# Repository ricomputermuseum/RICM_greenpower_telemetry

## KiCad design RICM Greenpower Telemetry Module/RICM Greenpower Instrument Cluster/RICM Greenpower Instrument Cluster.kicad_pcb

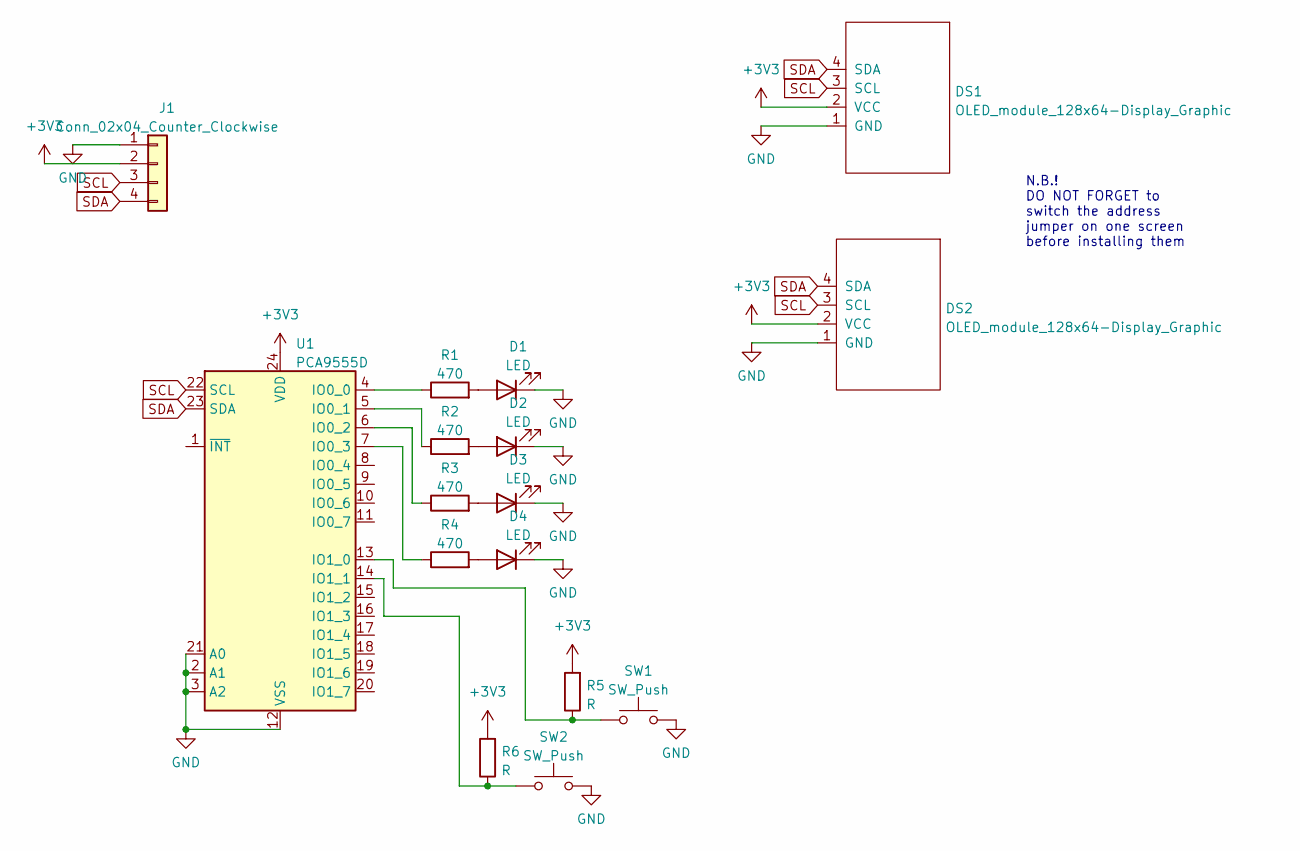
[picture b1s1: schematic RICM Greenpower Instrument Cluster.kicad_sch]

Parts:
D1, D2, D3, D4: LED; LED_D5.0mm
DS1, DS2: OLED_module_128x64-Display_Graphic; OLED__module_128x64
J1: Conn_02x04_Counter_Clockwise; PinHeader_1x04_P2.54mm_Vertical
R1, R2, R3, R4: 470; R_Axial_DIN0207_L6.3mm_D2.5mm_P7.62mm_Horizontal
R5, R6: R; R_Axial_DIN0207_L6.3mm_D2.5mm_P7.62mm_Horizontal
SW1, SW2: SW_Push; SW_PUSH_6mm_2pin
U1: PCA9555D; SOIC-24W_7.5x15.4mm_P1.27mm

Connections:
+3V3: DS1.2 (VCC), DS2.2 (VCC), J1.2, U1.24 (VDD)
+5V: R5.2, R6.2
GND: D1.1 (K), D2.1 (K), D3.1 (K), D4.1 (K), DS1.1 (GND), DS2.1 (GND), J1.1, SW1.2, SW2.2, U1.2 (A1), U1.3 (A2), U1.12 (VSS), U1.21 (A0)
unnamed: D1.2 (A), R1.2
unnamed: D2.2 (A), R2.2
unnamed: D3.2 (A), R3.2
unnamed: D4.2 (A), R4.2
unnamed: R1.1, U1.4 (IO0_0)
unnamed: R2.1, U1.5 (IO0_1)
unnamed: R3.1, U1.6 (IO0_2)
unnamed: R4.1, U1.7 (IO0_3)
unnamed: R5.1, SW1.1, U1.13 (IO1_0)
unnamed: R6.1, SW2.1, U1.14 (IO1_1)
SCL: DS1.3 (SCL), DS2.3 (SCL), J1.3, U1.22 (SCL)
SDA: DS1.4 (SDA), DS2.4 (SDA), J1.4, U1.23 (SDA)

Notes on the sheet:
N.B.! DO NOT FORGET to switch the address jumper on one screen before installing them

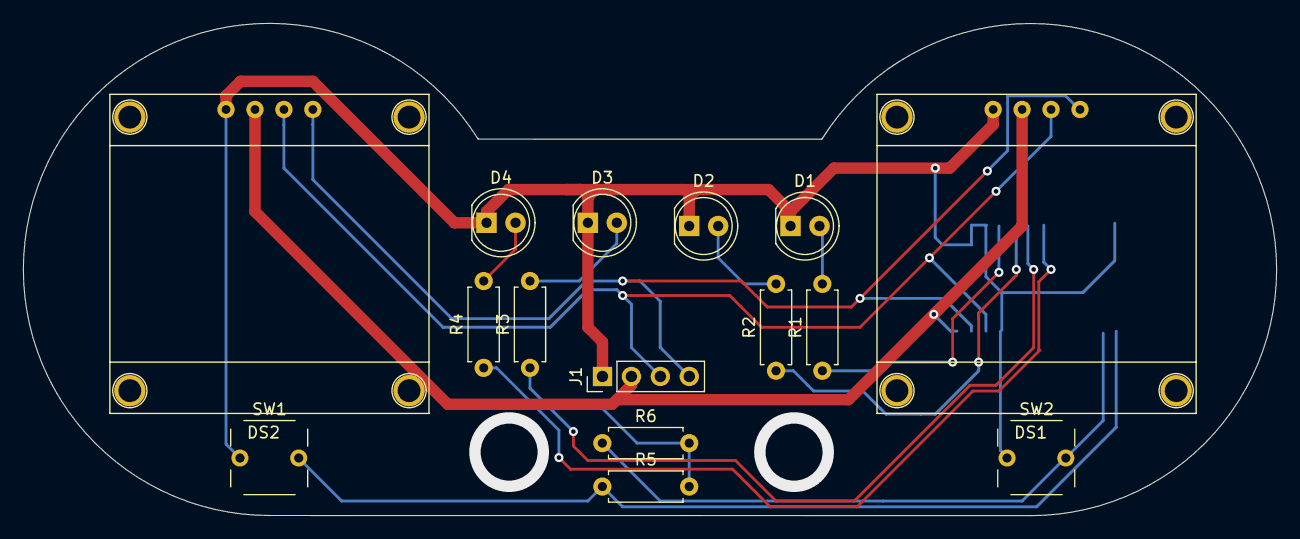
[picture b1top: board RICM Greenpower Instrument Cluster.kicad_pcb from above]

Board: 2 copper layers, 110.0 x 43.2 mm, 16 parts (1 on the bottom side), 15 nets.

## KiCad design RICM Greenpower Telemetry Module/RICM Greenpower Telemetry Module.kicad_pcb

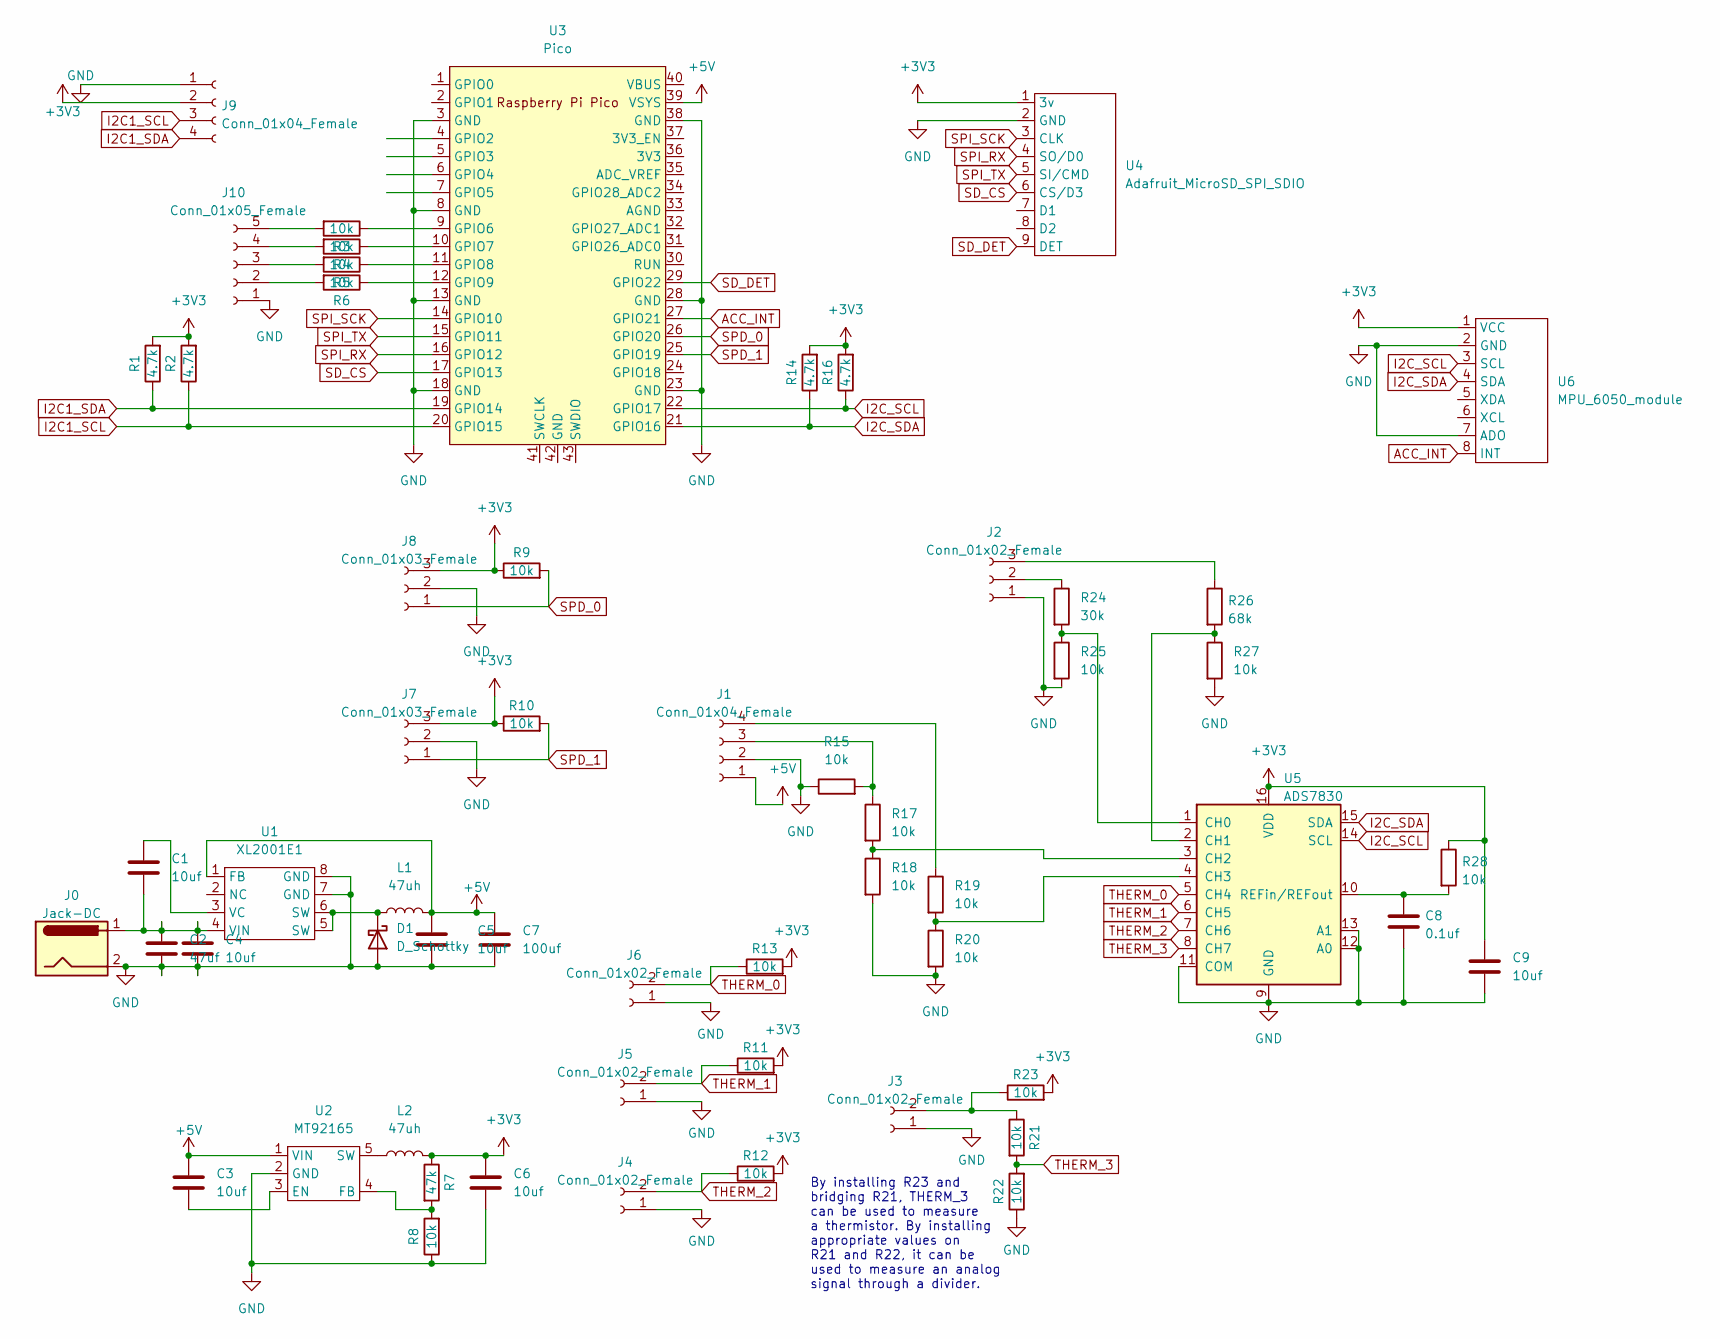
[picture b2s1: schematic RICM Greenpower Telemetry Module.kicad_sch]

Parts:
C1, C3, C4, C5, C6, C9: 10uf; C_0805_2012Metric
C2: 47uf; CP_Radial_D5.0mm_P2.00mm
C7: 100uf; CP_Radial_D8.0mm_P3.50mm
C8: 0.1uf; C_0805_2012Metric
D1: D_Schottky; D_SMA
J0: Jack-DC; BarrelJack_GCT_DCJ200-10-A_Horizontal
J1, J9: Conn_01x04_Female; PinHeader_1x04_P2.54mm_Vertical
J2: Conn_01x02_Female; PinHeader_1x03_P2.54mm_Vertical
J3, J4, J5, J6: Conn_01x02_Female; PinHeader_1x02_P2.54mm_Vertical
J7, J8: Conn_01x03_Female; PinHeader_1x03_P2.54mm_Vertical
J10: Conn_01x05_Female; PinHeader_1x05_P2.54mm_Vertical
L1, L2: 47uh; L_Axial_L12.0mm_D5.0mm_P15.24mm_Horizontal_Fastron_MISC
R1, R2, R14, R16: 4.7k; R_1206_3216Metric
R3, R4, R5, R6, R8, R9, R10, R11, R12, R13, R15, R17, R18, R19, R20, R21, R22, R23, R25, R27, R28: 10k; R_1206_3216Metric
R7: 47k; R_1206_3216Metric
R24: 30k; R_1206_3216Metric
R26: 68k; R_1206_3216Metric
U1: XL2001E1; SO-8_5.3x6.2mm_P1.27mm
U2: MT92165; SOT-23-5
U3: Pico; RPi_Pico_SMD_TH
U4: Adafruit_MicroSD_SPI_SDIO; Adafruit_MicroSD_breakout
U5: ADS7830; TSSOP-16_4.4x5mm_P0.65mm
U6: MPU_6050_module

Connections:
+3V3: C6.1, C9.1, J7.3, J8.3, J9.2, L2.2, R1.2, R2.2, R7.1, R9.1, R10.1, R11.2, R12.2, R13.2, R14.2, R16.2, R23.2, R28.1, U4.1 (3v), U5.16 (VDD), U6.1 (VCC)
+5V: C3.1, C5.1, C7.1, J1.1, L1.2, U1.1 (FB), U2.1 (VIN), U3.39 (VSYS)
ACC_INT: U3.27 (GPIO21), U6.8 (INT)
GND: C2.2, C4.2, C5.2, C6.2, C7.2, C8.1, C9.2, D1.2 (A), J0.2, J1.2, J2.1, J3.1, J4.1, J5.1, J6.1, J7.2, J8.2, J9.1, J10.1, R8.1, R15.1, R18.2, R20.2, R22.1, R25.2, R27.2, U1.7 (GND), U1.8 (GND), U2.2 (GND), U3.3 (GND), U3.8 (GND), U3.13 (GND), U3.18 (GND), U3.23 (GND), U3.28 (GND), U3.38 (GND), U4.2 (GND), U5.9 (GND), U5.11 (COM), U5.12 (A0), U5.13 (A1), U6.2 (GND), U6.7 (ADO)
I2C1_SCL: J9.3, R2.1, U3.20 (GPIO15)
I2C1_SDA: J9.4, R1.1, U3.19 (GPIO14)
I2C_SCL: R16.1, U3.22 (GPIO17), U5.14 (SCL), U6.3 (SCL)
I2C_SDA: R14.1, U3.21 (GPIO16), U5.15 (SDA), U6.4 (SDA)
unnamed: C1.1, U1.3 (VC)
unnamed: C1.2, C2.1, C4.1, J0.1, U1.4 (VIN)
unnamed: C3.2, U2.3 (EN)
unnamed: C8.2, R28.2, U5.10 (REFin/REFout)
unnamed: D1.1 (K), L1.1, U1.5 (SW), U1.6 (SW)
unnamed: J1.3, R15.2, R17.1
unnamed: J1.4, R19.1
unnamed: J2.2, R24.1
unnamed: J2.3, R26.1
unnamed: J3.2, R21.1, R23.1
unnamed: J10.2, R6.2
unnamed: J10.3, R5.2
unnamed: J10.4, R4.2
unnamed: J10.5, R3.2
unnamed: L2.1, U2.5 (SW)
unnamed: R3.1, U3.9 (GPIO6)
unnamed: R4.1, U3.10 (GPIO7)
unnamed: R5.1, U3.11 (GPIO8)
unnamed: R6.1, U3.12 (GPIO9)
unnamed: R7.2, R8.2, U2.4 (FB)
unnamed: R17.2, R18.1, U5.3 (CH2)
unnamed: R19.2, R20.1, U5.4 (CH3)
unnamed: R24.2, R25.1, U5.1 (CH0)
unnamed: R26.2, R27.1, U5.2 (CH1)
SD_CS: U3.17 (GPIO13), U4.6 (CS/D3)
SD_DET: U3.29 (GPIO22), U4.9 (DET)
SPD_0: J8.1, R9.2, U3.26 (GPIO20)
SPD_1: J7.1, R10.2, U3.25 (GPIO19)
SPI_RX: U3.16 (GPIO12), U4.4 (SO/D0)
SPI_SCK: U3.14 (GPIO10), U4.3 (CLK)
SPI_TX: U3.15 (GPIO11), U4.5 (SI/CMD)
THERM_0: J6.2, R13.1, U5.5 (CH4)
THERM_1: J5.2, R11.1, U5.6 (CH5)
THERM_2: J4.2, R12.1, U5.7 (CH6)
THERM_3: R21.2, R22.2, U5.8 (CH7)

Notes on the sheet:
By installing R23 and bridging R21, THERM_3 can be used to measure a thermistor. By installing appropriate values on R21 and R22, it can be used to measure an analog signal through a divider.

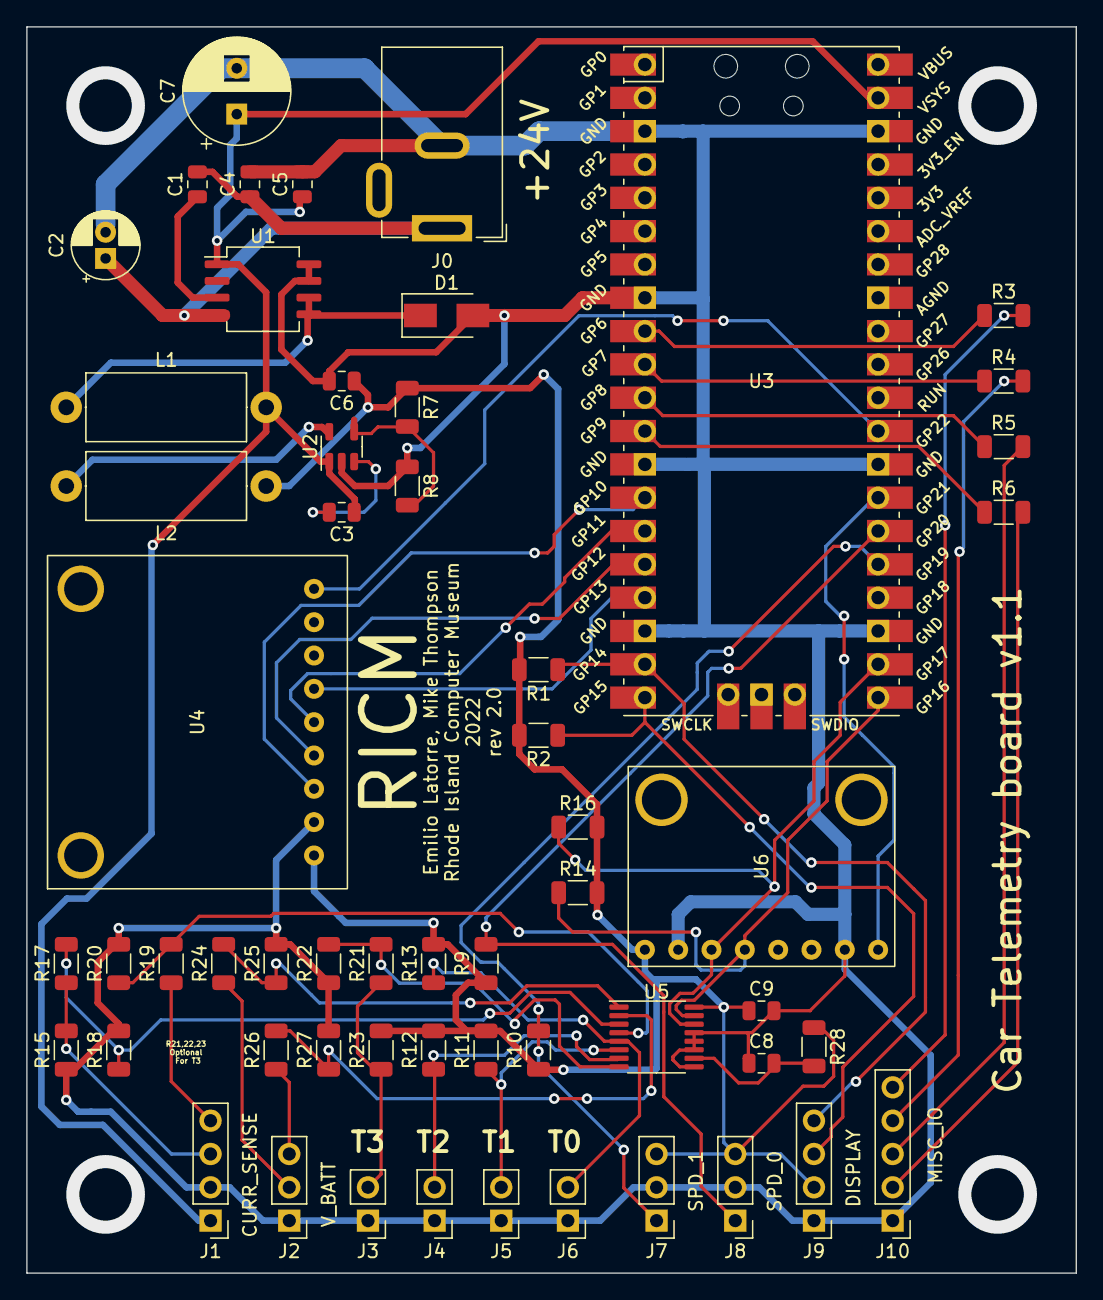
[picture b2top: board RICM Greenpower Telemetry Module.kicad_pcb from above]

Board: 2 copper layers, 80.0 x 95.0 mm, 57 parts (0 on the bottom side), 43 nets.

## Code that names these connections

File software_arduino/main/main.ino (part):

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#include <SPI.h>
#include <SD.h>
#define LOGFILE_NAME "/log.csv"
#define SD_CS_PIN 13
#define SD_DET_PIN 22 //high if a card is physically inserted
File logfile; //the file stream object for writing to the SD card
float data_to_log[16]; //the values of data to be formatted
char log_print_buf[16] = "              "; //buffer for formatted printing to the log file
void setupSD(){ //setup the SPI as connected to the SD card
  pinMode(SD_DET_PIN, INPUT);
  if(digitalRead(SD_DET_PIN)){ //only write if the SD card is inserted
    SPI1.setSCK(10); //using SPI1 on these pins
    SPI1.setTX(11);
    SPI1.setRX(12);
    SD.begin(SD_CS_PIN, SPI1); //the SD library offers hardware CS control. N.B. the SD stream can only be opened once, so if the SD card disconnects at any point a reset will be needed to begin logging again
    Serial.println(F("SD card stream initialized"));
    logfile = SD.open(LOGFILE_NAME, "a");
    logfile.println(F("speed,rpm,vBat0,vBat1,current,temp0,temp1,temp2,temp3,accX,accY,accZ,gyroX,gyroY,gyroZ,timestamp"));//column names go in the first row
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  }
}
void logToSD(){ //log the raw data in the buffer as formatted CSV data
  if(digitalRead(SD_DET_PIN)){ //only write if the SD card is inserted
    logfile = SD.open(LOGFILE_NAME, "a");
    if(SERIAL_LOGGING){ //if debugging is on, also print to serial
      Serial.println(F("speed,rpm,vBat1,vBat2,current,temp0,temp1,temp2,temp3,accX,accY,accZ,gyroX,gyroY,gyroZ,timestamp"));//column names go in the first row
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//spd_0 is for speed at the wheel, spd_1 is for motor RPM
#include <math.h>
#define WHEEL_DIAMTER_CM 40 //the total diameter of the outside of the tire at inflation pressure
#define INTERVAL_CONST_0 60000 //1rpm interval for spd_0, 60000/magnets per wheel
#define INTERVAL_CONST_1 15000 //1rpm interval for spd_0
float conversion_factor = ((((float)WHEEL_DIAMTER_CM * 3.14) * 60)/100000); //the total linear distance traveled by the tire in a minute converted to km, multiplied by RPM to get kilometers traveled per hour 
float speed = 0; //the vehicle speed in KPH
uint32_t intervals_0[] = {60001,60001,60001,60001,60001}; //median of 5 samples for a less noisy speed reading
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  }
}
void setupHall(){
  pinMode(20, INPUT); //SPD_0
  pinMode(19, INPUT); //SPD_1
  attachInterrupt(20, updateSpeedInterval0, FALLING); //update interval whenever the interrupt is triggered
  attachInterrupt(19, updateSpeedInterval1, FALLING); 
}
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
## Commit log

2022-05-19 started on a layout
2022-05-20 added most of the sensors we will probably want
    3x temperature sensors
    2x hall effect (for RPM)
    2x battery voltage
    1x current (inductive loop, 50A)
    1x 3-axis gyro
    1x 3-axis accelerometer
2022-05-21 added more sensors and connectors
    Added all the sensors and connectors that will go on this board (for now). Next step, layout
2022-05-22 bug fixes and missing connections
    Fixed the short from the first battery voltage to ground
    Added a chip select for interfacing the SD card over SPI
2022-05-23 first draft of layout
2022-05-24 Polyfuse and missing connections
2022-06-07 laid out dial cluster
2022-07-13 update cluster
    Updated cluster schematic to use an I2C gpio expander. Added two pushbutton switches.
2022-07-30 added onboard regulator
    Added onboard regulator and associated components. Added 4th thermistor connector.
2022-08-05 rearranged board to fit regulator
2022-08-06 tightened up spacing on the board
2022-08-08 last revisions before first order
2022-08-08 Added pullups for i2c
2022-08-08 started work on software
    Copied over the libraries for the gpio and oled modules. Added a library for the ADC chip. Started working on a module for the hall effect speedometer.
2022-08-09 more libraries
    Worked on the hall sensor and added a library for the thermistor.
2022-08-12 rearranged board
    Switched to sdm resistors and capacitors. Added a 3v3 regulated supply. Various other revisions.
2022-09-03 Moving to laptop
2022-10-23 Updates to ADC, gyro, thermistor libraries
2022-10-23 fixed errors discovered in v1 board
    Connected vref on the ADS7830 to 3v3.
    Corrected swapped pins on MT9216.
    Added silkscreens and readjusted connector numbering.
2022-11-21 work on thermistor calculation
2022-12-04 added diags, bugfixes
    Added libraries and associated diagnostics for OLED screens and GPIO buttons.
2023-01-24 Updates to SD card
    Added library for SD card and began work on library for CSV formatting
2023-01-25 SD card read and write working
    SD card wrapper now writes and reads correctly
2023-02-02 updates to SD utilites
2023-04-11 PDF of main circuit diagram
2023-04-19 added BOMs from LCSC
2023-07-21 initial hall sensor support
2024-01-13 Fixed footprints and silkscreen
2024-01-16 updated hall library
    Moved hall library to an interrupt-updated interval calculation
2024-07-11 Moving to Arduino Core
    Moving from Micropython to Arduino core. Better library support, runs faster, and better tutorials and example code available for when the students want to edit it later.
    Set out a main outline with scheduling and debug prints.
2024-07-11 Fixed typos
2024-07-12 SD card datalogging
    SD card data logging added. Data from all sensors is logged in CSV format with stamp of elapsed time since last reset.
    0s are entered for sensors that are not reading or have not yet been configured.
2024-07-12 Thermistor temperature array
    Calculated and added thermistor temperature values in a header. As the equation of temperature-resistance for the thermistor is roughly quartic, the adc is only 8 bits, and we have a large amount of 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
2024-07-14 Added ADC and thermistor support
    Set up the ADS7830 ADC on the board. Added function for reading NTC thermistors as wired on the board and converting the reading to a celcius temperature for logging. Recalculated and corrected therm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
2024-07-14 Hall effect sensors working
    Created functionality for reading a periodic signal from a hall effect sensor and associated functions to convert to RPM and speed for logging.
2024-07-14 Added Battery and Current measurements
    Added functionality for measuring battery voltages through the ADC chip and current using the current sensor.
2024-07-16 Gyro/accelerometer support
    Added support for reading accelerometer and gyroscopic data on the MPU6050 chip
2024-07-16 Schematic and layout corrections
    Added revision silkscreen to schematic. Fixed pinout of display connector to match standard i2c pinout. Added schematic notes explaining resistor options for THERM_3.
2024-07-16 Similar corrections for display module
    Fixed pinout and updated silkscreen and notes for the display module schematic and board.
2024-07-16 Added display support
    Added support for the OLEDS, buttons, and LEDS on the display module.
